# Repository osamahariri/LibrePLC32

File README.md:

# LibrePLC32

**LibrePLC32** is an open-source, KiCad-based Programmable Logic Controller (PLC) hardware project.

The goal of the project is to create a compact, hackable, and well-documented PLC platform for industrial automation experiments, prototyping, education, and open hardware development.

> ⚠️ **Work in progress:** LibrePLC32 is currently under development.

## Project goals

LibrePLC32 aims to provide:

- An open hardware PLC design
- KiCad source files for schematic and PCB development
- Field-oriented interfaces such as digital I/O, isolated CAN, isolated RS-485, and Ethernet
- A design that can be studied, modified, repaired, and improved by the community
- Documentation for design decisions and component calculations

## Repository structure

```text
.
├── img/              # Project logo and graphics
├── plc/
│   ├── docs/         # Design notes and calculations
│   └── kicad/        # KiCad project, schematics, PCB, and libraries
├── LICENSE
└── README.md
```

## Features

LibrePLC32 is designed to provide a practical set of PLC-oriented hardware features:

- **8–36 V DC input voltage range**
- **4 isolated digital inputs** for field signals
- **4 transistor digital outputs** for driving external loads
- **2 relay output terminals** for switching isolated loads
- **Isolated RS-485 interface** for industrial serial communication
- **Isolated CAN bus interface** for device-to-device communication
- **Ethernet interface** for network connectivity

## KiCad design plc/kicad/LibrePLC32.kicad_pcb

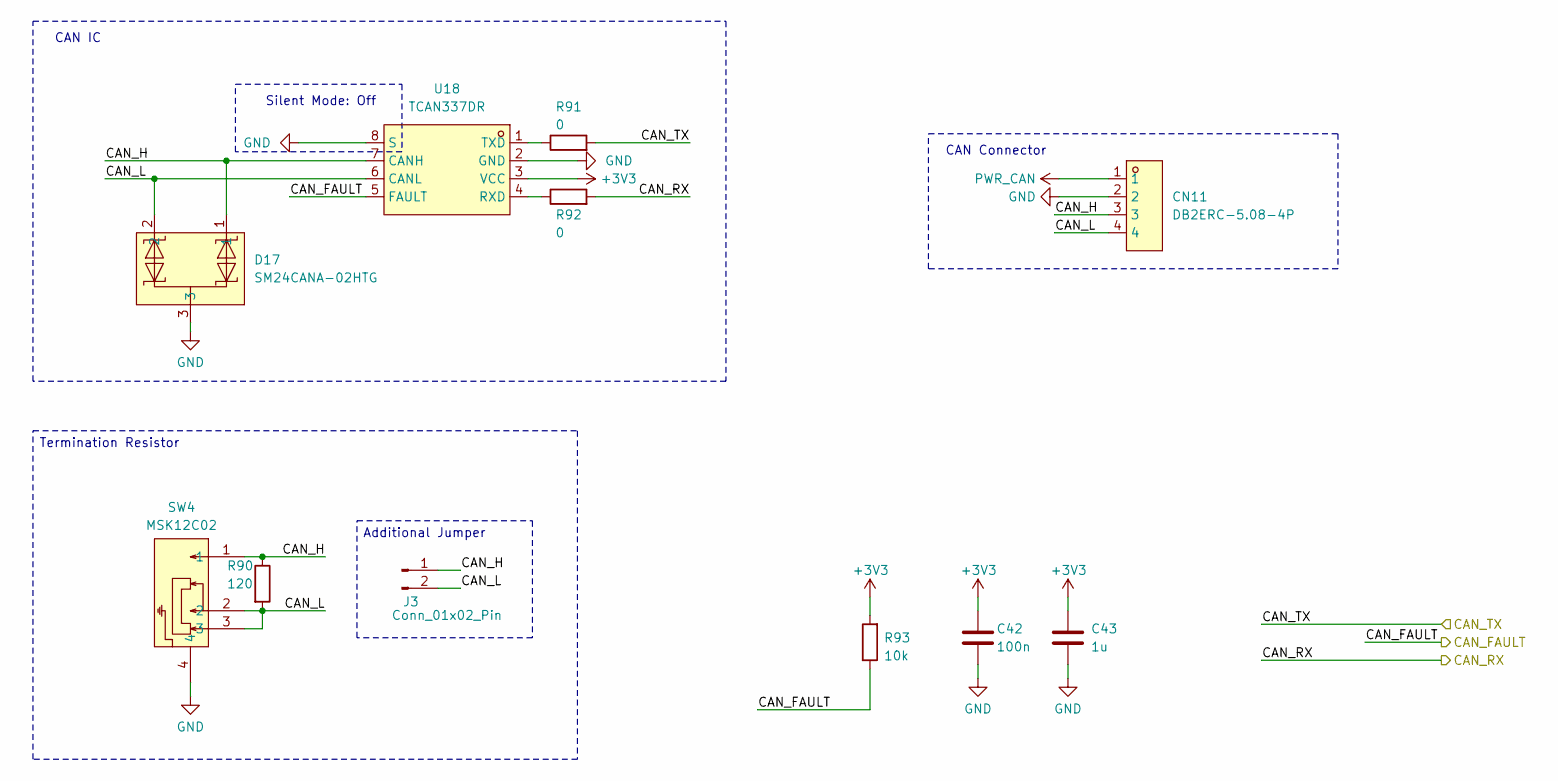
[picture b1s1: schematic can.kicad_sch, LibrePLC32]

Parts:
C42: 100n; C_0603_1608Metric
C43: 1u; C_0603_1608Metric
CN11: DB2ERC-5.08-4P; CONN-TH_4P-P5.08_DB2ERC-5.08-4P; MPN DB2ERC-5.08-4P-GN; LCSC Part C395753
D17: SM24CANA-02HTG; SOT-23_L2.9-W1.3-P1.90-LS2.4-BR; MPN SM24CANA-02HTG; LCSC Part C151236
J3: Conn_01x02_Pin; PinSocket_1x02_P2.54mm_Vertical
R90: 120; R_0603_1608Metric
R91, R92: 0; R_0603_1608Metric
R93: 10k; R_0603_1608Metric
SW4: MSK12C02; SW-TH_MSK12C02; MPN MSK12C02; LCSC Part C431540
U18: TCAN337DR; SOIC-8_L4.9-W3.9-P1.27-LS6.0-BL; MPN TCAN337DR; LCSC Part C2860648

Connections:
+3V3: C42.1, C43.1, R93.2, U18.3 (VCC); also elsewhere on the board
/CAN/CAN_FAULT: R93.1, U18.5 (FAULT); also elsewhere on the board
/CAN/CAN_H: CN11.3, D17.1, J3.1, R90.1, SW4.1, U18.7 (CANH)
/CAN/CAN_L: CN11.4, D17.2, J3.2, R90.2, SW4.2, SW4.3, U18.6 (CANL)
/CAN/CAN_RX: R92.2; also elsewhere on the board
/CAN/CAN_TX: R91.2; also elsewhere on the board
GND: C42.2, C43.2, CN11.2, D17.3, SW4.4, U18.2 (GND), U18.8 (S); also elsewhere on the board
unnamed: R92.1, U18.4 (RXD)
unnamed: R91.1, U18.1 (TXD)
PWR_CAN: CN11.1; also elsewhere on the board

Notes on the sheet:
CAN Connector
Additional Jumper
Termination Resistor
CAN IC
Silent Mode: Off

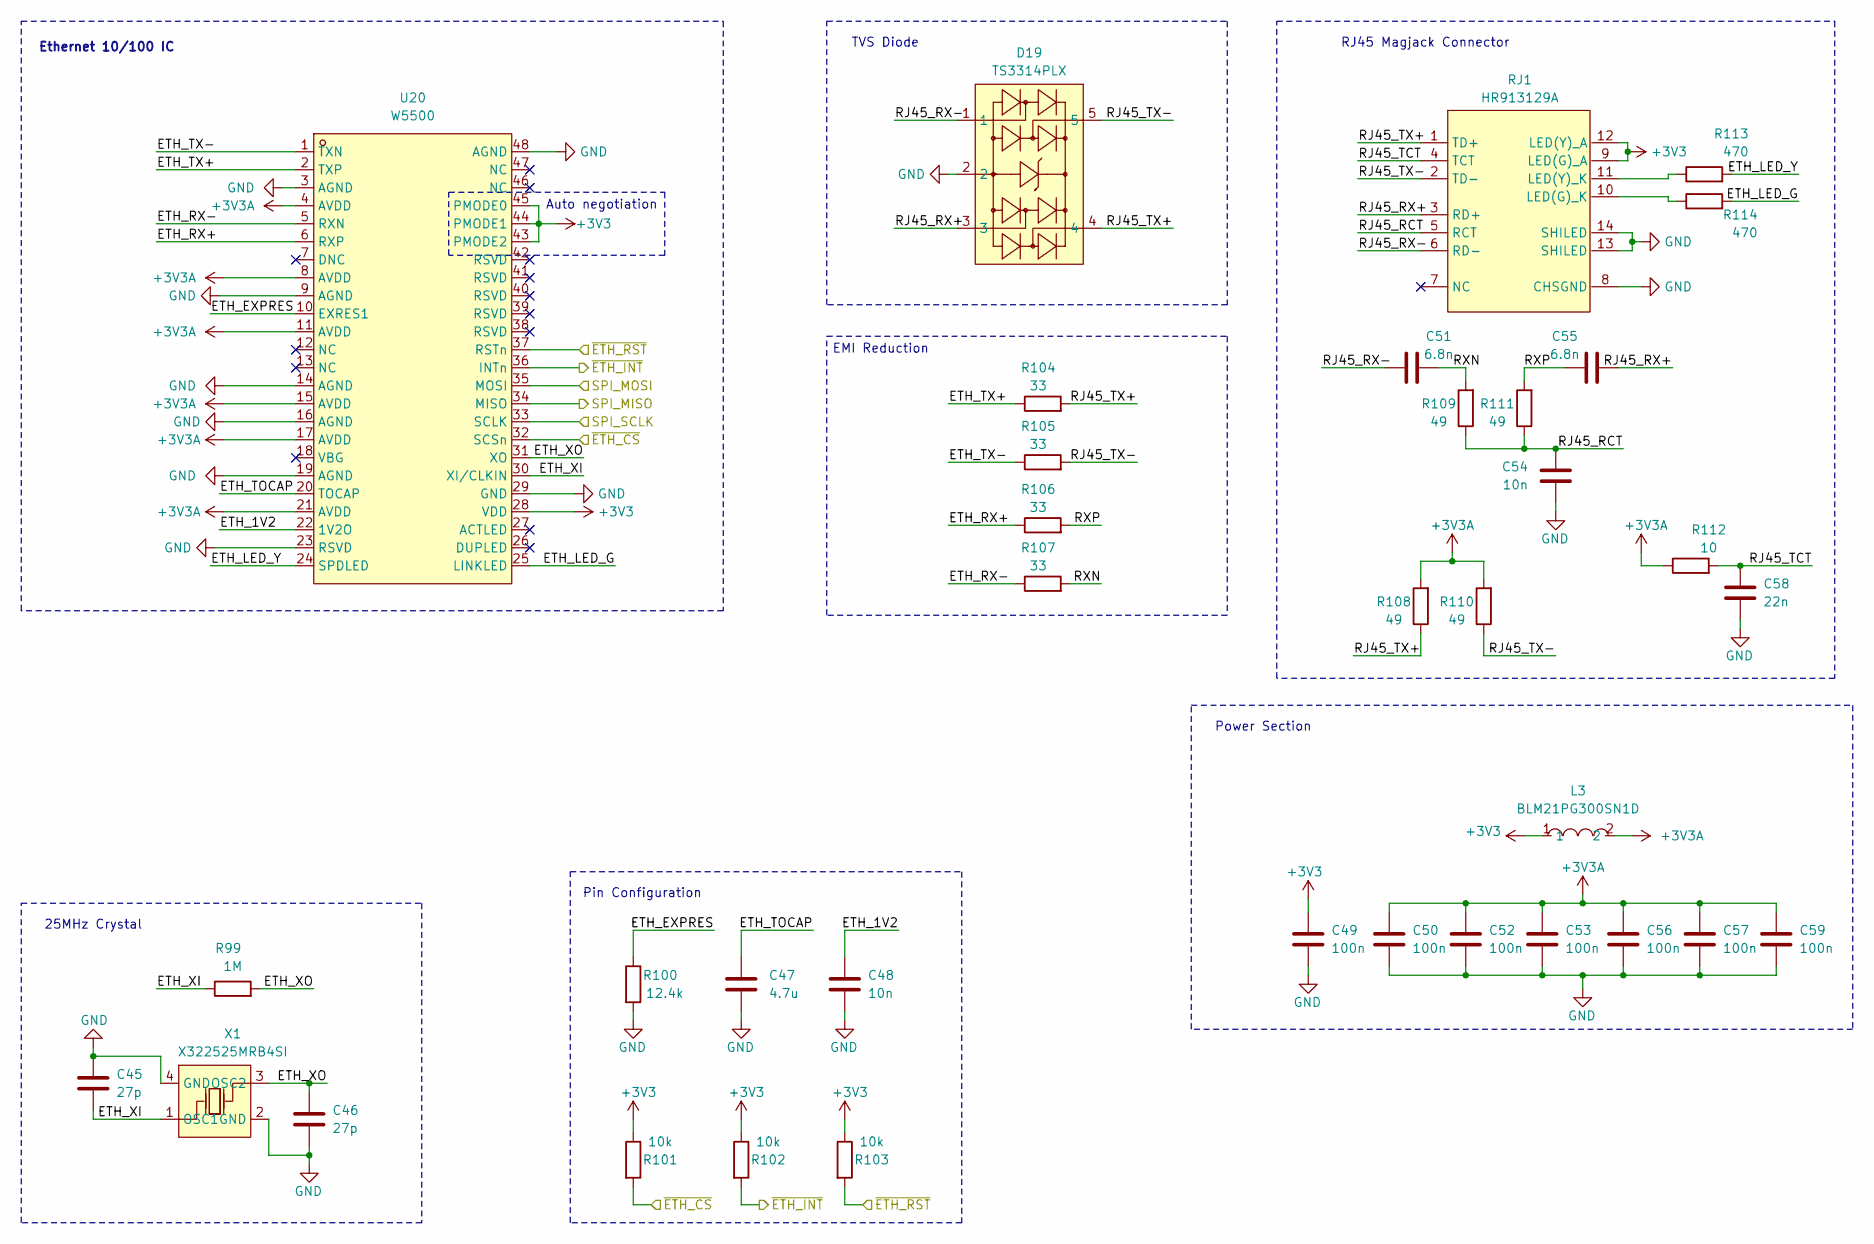
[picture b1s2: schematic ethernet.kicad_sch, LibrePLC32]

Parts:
C45, C46: 27p; C_0603_1608Metric
C47: 4.7u; C_0603_1608Metric
C48, C54: 10n; C_0603_1608Metric
C49, C50, C52, C53, C56, C57, C59: 100n; C_0603_1608Metric
C51, C55: 6.8n; C_0603_1608Metric
C58: 22n; C_0603_1608Metric
D19: TS3314PLX; SOT-23-5_L2.9-W1.6-P0.95-LS2.8-BR; MPN TS3314PLX; LCSC Part C5156700
L3: BLM21PG300SN1D; L0805; MPN BLM21PG300SN1D; LCSC Part C16903
R99: 1M; R_0603_1608Metric
R100: 12.4k; R_0603_1608Metric
R101, R102, R103: 10k; R_0603_1608Metric
R104, R105, R106, R107: 33; R_0603_1608Metric
R108, R109, R110, R111: 49; R_0603_1608Metric
R112: 10; R_0603_1608Metric
R113, R114: 470; R_0603_1608Metric
RJ1: HR913129A; RJ45-TH_HR913129A; MPN HR913129A; LCSC Part C70302
U20: W5500; LQFP-48_L7.0-W7.0-P0.50-LS9.0-BL; MPN W5500; LCSC Part C32843
X1: X322525MRB4SI; OSC-SMD_4P-L3.2-W2.5-BL_SIT8008BI; MPN X322525MRB4SI; LCSC Part C70593

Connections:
+3V3: C49.1, L3.1, R101.1, R102.1, R103.1, RJ1.9 (LED(G)_A), RJ1.12 (LED(Y)_A), U20.28 (VDD), U20.43 (PMODE2), U20.44 (PMODE1), U20.45 (PMODE0); also elsewhere on the board
+3V3A: C50.1, C52.1, C53.1, C56.1, C57.1, C59.1, L3.2, R108.2, R110.2, R112.1, U20.4 (AVDD), U20.8 (AVDD), U20.11 (AVDD), U20.15 (AVDD), U20.17 (AVDD), U20.21 (AVDD)
/Ethernet/ETH_1V2: C48.1, U20.22 (1V2O)
/Ethernet/ETH_EXPRES: R100.1, U20.10 (EXRES1)
/Ethernet/ETH_LED_G: R114.2, U20.25 (LINKLED)
/Ethernet/ETH_LED_Y: R113.2, U20.24 (SPDLED)
/Ethernet/ETH_RX+: R106.1, U20.6 (RXP)
/Ethernet/ETH_RX-: R107.1, U20.5 (RXN)
/Ethernet/ETH_TOCAP: C47.1, U20.20 (TOCAP)
/Ethernet/ETH_TX+: R104.1, U20.2 (TXP)
/Ethernet/ETH_TX-: R105.1, U20.1 (TXN)
/Ethernet/ETH_XI: C45.2, R99.1, U20.30 (XI/CLKIN), X1.1 (OSC1)
/Ethernet/ETH_XO: C46.1, R99.2, U20.31 (XO), X1.3 (OSC2)
/Ethernet/RJ45_RCT: C54.1, R109.1, R111.1, RJ1.5 (RCT)
/Ethernet/RJ45_RX+: C55.2, D19.3, RJ1.3 (RD+)
/Ethernet/RJ45_RX-: C51.2, D19.1, RJ1.6 (RD-)
/Ethernet/RJ45_TCT: C58.1, R112.2, RJ1.4 (TCT)
/Ethernet/RJ45_TX+: D19.4, R104.2, R108.1, RJ1.1 (TD+)
/Ethernet/RJ45_TX-: D19.5, R105.2, R110.1, RJ1.2 (TD-)
/Ethernet/RXN: C51.1, R107.2, R109.2
/Ethernet/RXP: C55.1, R106.2, R111.2
/Ethernet/SPI_MISO: U20.34 (MISO); also elsewhere on the board
/Ethernet/SPI_MOSI: U20.35 (MOSI); also elsewhere on the board
/Ethernet/SPI_SCLK: U20.33 (SCLK); also elsewhere on the board
/Ethernet/~ETH_CS: R101.2, U20.32 (SCSn); also elsewhere on the board
/Ethernet/~ETH_INT: R102.2, U20.36 (INTn); also elsewhere on the board
/Ethernet/~ETH_RST: R103.2, U20.37 (RSTn); also elsewhere on the board
GND: C45.1, C46.2, C47.2, C48.2, C49.2, C50.2, C52.2, C53.2, C54.2, C56.2, C57.2, C58.2, C59.2, D19.2, R100.2, RJ1.8 (CHSGND), RJ1.13 (SHILED), RJ1.14 (SHILED), U20.3 (AGND), U20.9 (AGND), U20.14 (AGND), U20.16 (AGND), U20.19 (AGND), U20.23 (RSVD), U20.29 (GND), U20.48 (AGND), X1.2 (GND), X1.4 (GND); also elsewhere on the board
unnamed: R114.1, RJ1.10 (LED(G)_K)
unnamed: R113.1, RJ1.11 (LED(Y)_K)

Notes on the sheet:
Auto negotiation
Ethernet 10/100 IC
EMI Reduction
TVS Diode
Power Section
Pin Configuration
25MHz Crystal
RJ45 Magjack Connector

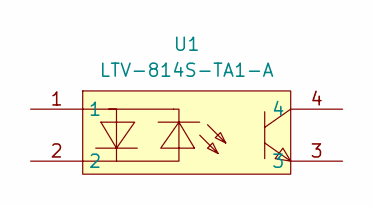
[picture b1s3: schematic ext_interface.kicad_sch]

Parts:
U1: LTV-814S-TA1-A; OPTO-SMD-4_L4.6-W6.5-P2.54-LS10.3-BL; MPN LTV-814S-TA1-A; LCSC Part C108051

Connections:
/Terminal Blocks Interface/T1_EN1: U1.4 (P00); also elsewhere on the board
/Terminal Blocks Interface/~GPIO_MUX_INT: U1.1 (~INT); also elsewhere on the board
GND: U1.2 (A1), U1.3 (A2); also elsewhere on the board

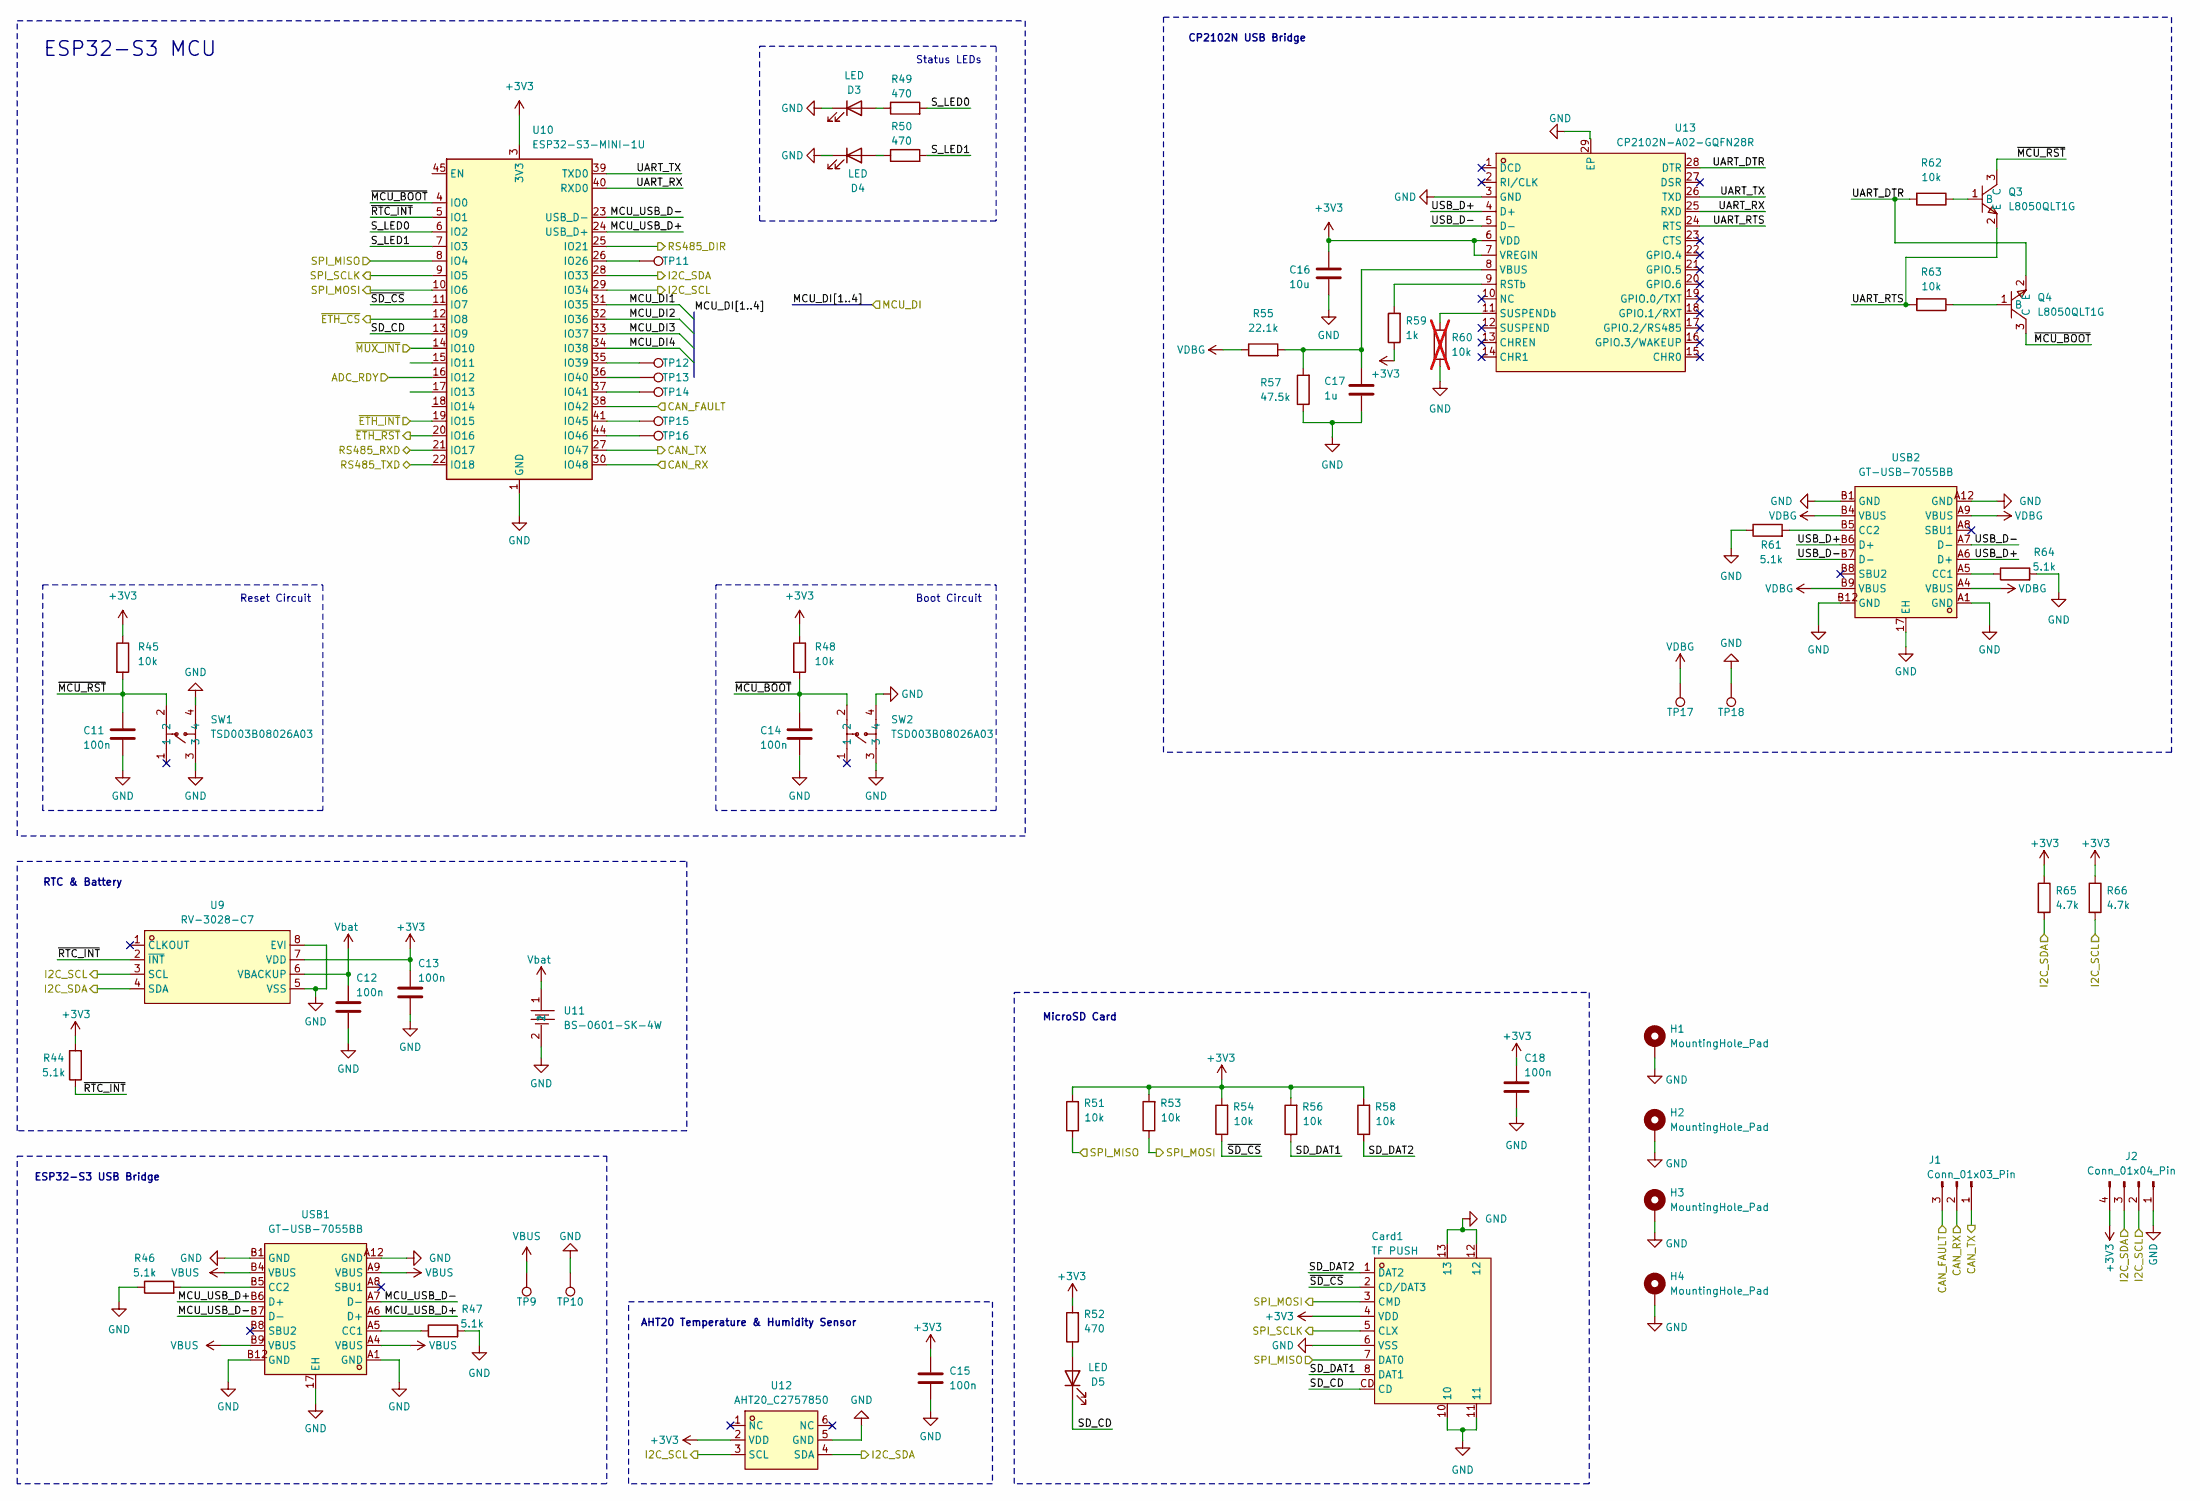
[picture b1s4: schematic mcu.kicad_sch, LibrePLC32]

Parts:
C11, C12, C13, C14, C15, C18: 100n; C_0603_1608Metric
C16: 10u; C_0603_1608Metric
C17: 1u; C_0603_1608Metric
Card1: TF PUSH; TF-SMD_TF-PUSH; MPN TF PUSH; LCSC Part C393941
D3, D4, D5: LED; LED_0805_2012Metric
H1, H2, H3, H4: MountingHole_Pad; MountingHole_4.3mm_M4_DIN965_Pad_TopBottom
J1: Conn_01x03_Pin
J2: Conn_01x04_Pin; PinSocket_1x04_P2.54mm_Vertical
Q3, Q4: L8050QLT1G; SOT-23-3_L2.9-W1.3-P1.90-LS2.4-BR; MPN L8050QLT1G; LCSC Part C49581
R44, R46, R47, R61, R64: 5.1k; R_0603_1608Metric
R45, R48, R51, R53, R54, R56, R58, R62, R63: 10k; R_0603_1608Metric
R49, R50, R52: 470; R_0603_1608Metric
R55: 22.1k; R_0603_1608Metric
R57: 47.5k; R_0603_1608Metric
R59: 1k; R_0603_1608Metric
R60: 10k; R_0603_1608Metric; not fitted
R65, R66: 4.7k; R_0603_1608Metric
SW1, SW2: TSD003B08026A03; SW-SMD_4P-L6.0-W6.0-P4.50-LS8.6; MPN TSD003B08026A03; LCSC Part C2888805
TP9, TP10, TP17, TP18: TestPoint; TestPoint_Pad_D3.0mm
TP11, TP12, TP13, TP14, TP15, TP16: TestPoint; TestPoint_Pad_D2.0mm
U9: RV-3028-C7; OSC-SMD_8P-L3.2-W1.5-P0.90-BL; MPN RV-3028-C7-32.768kHz-1ppm-TA-QC; LCSC Part C3019759
U10: ESP32-S3-MINI-1U; BULETM-SMD_ESPRESSIF_ESP32-S3-MINI-1U-N8
U11: BS-0601-SK-4W; BAT-SMD_BS-06-B4AA012; MPN BS-0601-SK-4W; LCSC Part C19089122
U12: AHT20_C2757850; SENSOR-SMD_L3.0-W3.0-P1.00-BR; MPN AHT20; LCSC Part C2757850
U13: CP2102N-A02-GQFN28R; QFN-28_L5.0-W5.0-P0.50-TL-EP3.3; MPN CP2102N-A02-GQFN28R; LCSC Part C964632
USB1, USB2: GT-USB-7055BB; USB-C-TH_GT-USB-7055BB; MPN GT-USB-7055BB; LCSC Part C7450621

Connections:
+3V3: C13.2, C15.1, C16.2, C18.2, Card1.4 (VDD), J2.4, R44.2, R45.1, R48.1, R51.2, R52.2, R53.2, R54.2, R56.2, R58.2, R59.1, R65.1, R66.1, U9.7 (VDD), U10.3 (3V3), U12.2 (VDD), U13.6 (VDD), U13.7 (VREGIN); also elsewhere on the board
/CAN/CAN_FAULT: J1.3, U10.38 (IO42); also elsewhere on the board
/CAN/CAN_RX: J1.2, U10.30 (IO48); also elsewhere on the board
/CAN/CAN_TX: J1.1, U10.27 (IO47); also elsewhere on the board
/Ethernet/SPI_MISO: Card1.7 (DAT0), R51.1, U10.8 (IO4); also elsewhere on the board
/Ethernet/SPI_MOSI: Card1.3 (CMD), R53.1, U10.10 (IO6); also elsewhere on the board
/Ethernet/SPI_SCLK: Card1.5 (CLX), U10.9 (IO5); also elsewhere on the board
/Ethernet/~ETH_CS: U10.12 (IO8); also elsewhere on the board
/Ethernet/~ETH_INT: U10.19 (IO15); also elsewhere on the board
/Ethernet/~ETH_RST: U10.20 (IO16); also elsewhere on the board
/MCU/ADC_RDY: U10.16 (IO12); also elsewhere on the board
/MCU/I2C_SCL: J2.2, R66.2, U9.3 (SCL), U10.29 (IO34), U12.3 (SCL); also elsewhere on the board
/MCU/I2C_SDA: J2.3, R65.2, U9.4 (SDA), U10.28 (IO33), U12.4 (SDA); also elsewhere on the board
/MCU/MCU_DI1: U10.31 (IO35); also elsewhere on the board
/MCU/MCU_DI2: U10.32 (IO36); also elsewhere on the board
/MCU/MCU_DI3: U10.33 (IO37); also elsewhere on the board
/MCU/MCU_DI4: U10.34 (IO38); also elsewhere on the board
/MCU/MCU_USB_D+: U10.24 (USB_D+), USB1.A6 (D+), USB1.B6 (D+)
/MCU/MCU_USB_D-: U10.23 (USB_D-), USB1.A7 (D-), USB1.B7 (D-)
/MCU/SD_CD: Card1.CD, D5.1 (K), U10.13 (IO9)
/MCU/SD_DAT1: Card1.8 (DAT1), R56.1
/MCU/SD_DAT2: Card1.1 (DAT2), R58.1
/MCU/S_LED0: R49.2, U10.6 (IO2)
/MCU/S_LED1: R50.2, U10.7 (IO3)
/MCU/UART_DTR: Q4.2 (E), R62.2, U13.28 (DTR)
/MCU/UART_RTS: Q3.2 (E), R63.2, U13.24 (RTS)
/MCU/UART_RX: U10.40 (RXD0), U13.25 (RXD)
/MCU/UART_TX: U10.39 (TXD0), U13.26 (TXD)
/MCU/USB_D+: U13.4 (D+), USB2.A6 (D+), USB2.B6 (D+)
/MCU/USB_D-: U13.5 (D-), USB2.A7 (D-), USB2.B7 (D-)
/MCU/~MCU_BOOT: C14.2, Q4.3 (C), R48.2, SW2.2, U10.4 (IO0)
/MCU/~MCU_RST: C11.2, Q3.3 (C), R45.2, SW1.2
/MCU/~RTC_INT: R44.1, U9.2 (~INT), U10.5 (IO1)
/MCU/~SD_CS: Card1.2 (CD/DAT3), R54.1, U10.11 (IO7)
/RS-485/RS485_DIR: U10.25 (IO21); also elsewhere on the board
/RS-485/RS485_RXD: U10.21 (IO17); also elsewhere on the board
/RS-485/RS485_TXD: U10.22 (IO18); also elsewhere on the board
/Terminal Blocks Interface/~GPIO_MUX_INT: U10.14 (IO10); also elsewhere on the board
GND: C11.1, C12.1, C13.1, C14.1, C15.2, C16.1, C17.2, C18.1, Card1.6 (VSS), Card1.10, Card1.11, Card1.12, Card1.13, D3.1 (K), D4.1 (K), H1.1 (1_1), H2.1 (1_1), H3.1 (1_1), H4.1 (1_1), J2.1, R46.1, R47.2, R57.1, R60.1, R61.1, R64.2, SW1.3, SW1.4, SW2.3, SW2.4, TP10.1 (1_1), TP18.1 (1_1), U9.5 (VSS), U9.8 (EVI), U10.1 (GND), U10.2 (GND), U10.42 (GND), U10.43 (GND), U10.46 (GND), U10.47 (GND), U10.48 (GND), U10.49 (GND), U10.50 (GND), U10.51 (GND), U10.52 (GND), U10.53 (GND), U10.54 (GND), U10.55 (GND), U10.56 (GND), U10.57 (GND), U10.58 (GND), U10.59 (GND), U10.60 (GND), U10.61 (GND), U10.62 (GND), U10.63 (GND), U10.64 (GND), U10.65 (GND), U11.2, U12.5 (GND), U13.3 (GND), U13.29 (EP), USB1.17 (EH), USB1.A1 (GND), USB1.A12 (GND), USB1.B1 (GND), USB1.B12 (GND), USB2.17 (EH), USB2.A1 (GND), USB2.A12 (GND), USB2.B1 (GND), USB2.B12 (GND); also elsewhere on the board
unnamed: D3.2 (A), R49.1
unnamed: D4.2 (A), R50.1
unnamed: D5.2 (A), R52.1
unnamed: Q3.1 (B), R62.1
unnamed: Q4.1 (B), R63.1
unnamed: TP11.1 (1_1), U10.26 (IO26)
unnamed: TP12.1 (1_1), U10.35 (IO39)
unnamed: TP13.1 (1_1), U10.36 (IO40)
unnamed: TP14.1 (1_1), U10.37 (IO41)
unnamed: TP15.1 (1_1), U10.41 (IO45)
unnamed: TP16.1 (1_1), U10.44 (IO46)
unnamed: R59.2, U13.9 (RSTb)
unnamed: R60.2, U13.11 (SUSPENDb)
unnamed: C17.1, R55.2, R57.2, U13.8 (VBUS)
unnamed: R47.1, USB1.A5 (CC1)
unnamed: R46.2, USB1.B5 (CC2)
unnamed: R64.1, USB2.A5 (CC1)
unnamed: R61.2, USB2.B5 (CC2)
VBUS: TP9.1 (1_1), USB1.A4 (VBUS), USB1.A9 (VBUS), USB1.B4 (VBUS), USB1.B9 (VBUS); also elsewhere on the board
VDBG: R55.1, TP17.1 (1_1), USB2.A4 (VBUS), USB2.A9 (VBUS), USB2.B4 (VBUS), USB2.B9 (VBUS); also elsewhere on the board
Vbat: C12.2, U9.6 (VBACKUP), U11.1

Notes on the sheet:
MicroSD Card
Status LEDs
AHT20 Temperature & Humidity Sensor
Reset Circuit
RTC & Battery
CP2102N USB Bridge
Boot Circuit
ESP32-S3 USB Bridge
ESP32-S3 MCU

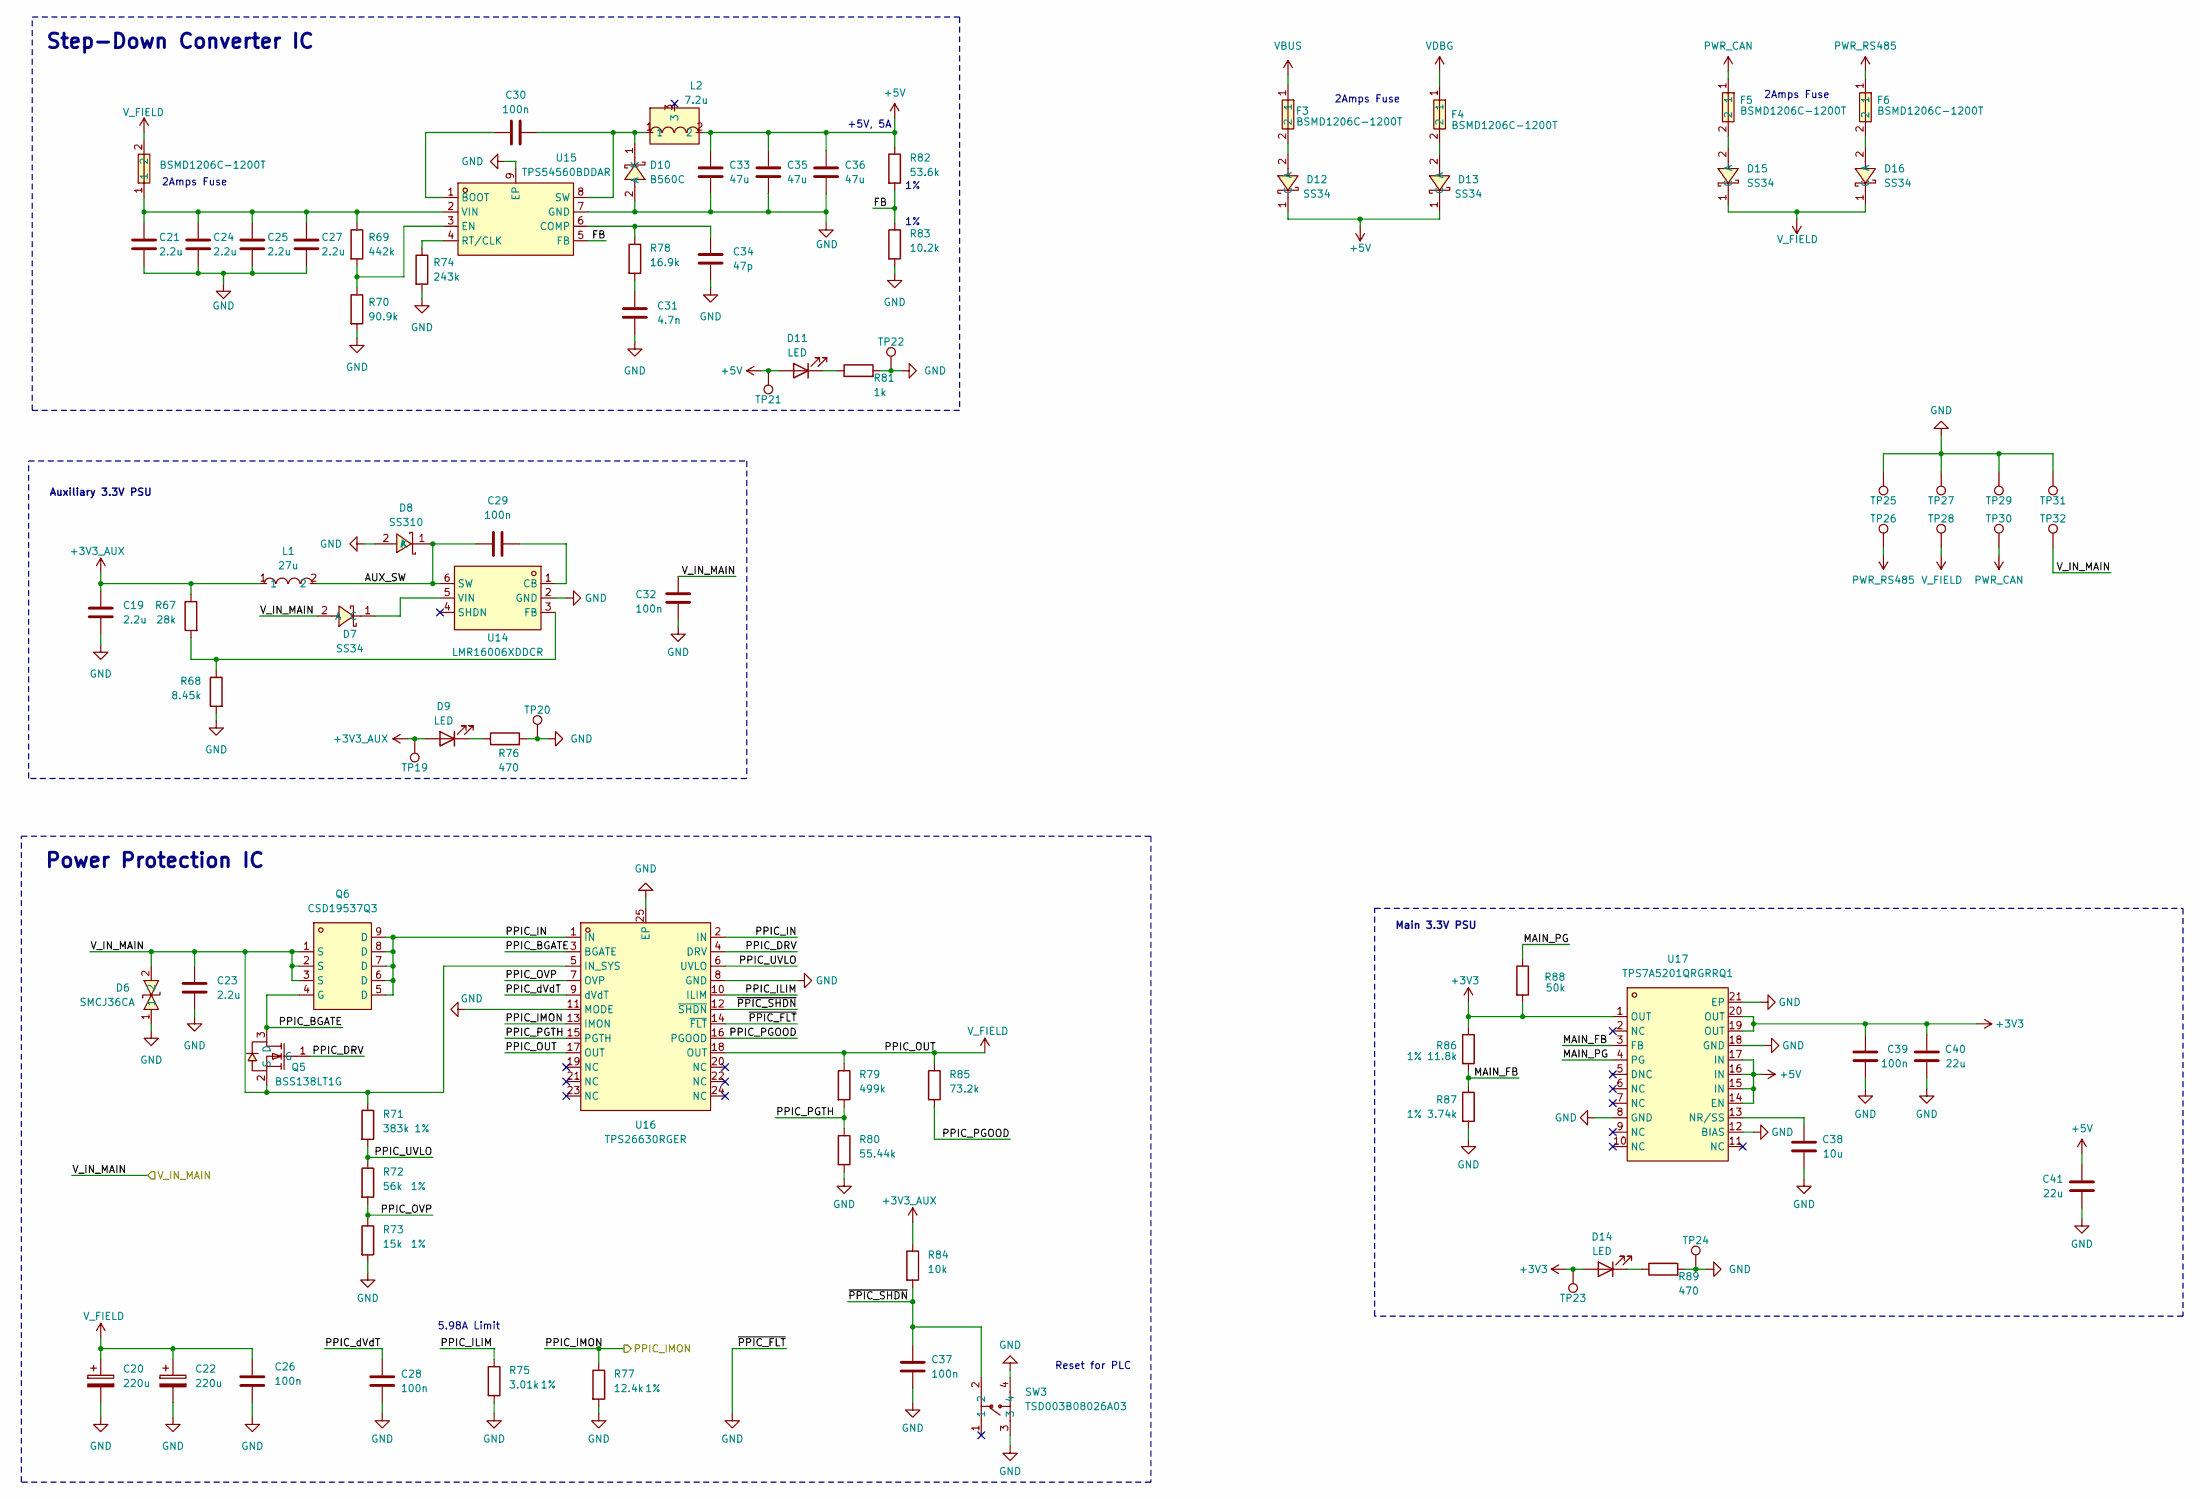
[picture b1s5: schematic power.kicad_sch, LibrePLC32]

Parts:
C19, C23: 2.2u; C_1206_3216Metric
C20, C22: 220u; C_Elec_10x10.2; LCSC Part C125977
C21, C24, C25, C27: 2.2u; C_0603_1608Metric
C26, C28, C29, C30, C32, C37, C39: 100n; C_0603_1608Metric
C31: 4.7n; C_0603_1608Metric
C33, C35, C36: 47u; C_0603_1608Metric
C34: 47p; C_0603_1608Metric
C38: 10u; C_0603_1608Metric
C40: 22u; C_0603_1608Metric; LCSC Part C86295
C41: 22u; C_0603_1608Metric
D6: SMCJ36CA; SMC_L6.9-W5.9-LS7.9-BI; MPN SMCJ36CA; LCSC Part C151283
D7, D12, D13, D15, D16: SS34; SMA_L4.3-W2.7-LS5.1-RD; MPN SS34; LCSC Part C908680
D8: SS310; SMB_L4.6-W3.6-LS5.3-RD; MPN SS310B; LCSC Part C14281
D9, D11, D14: LED; LED_0805_2012Metric
D10: B560C; SMC_L6.9-W5.9-LS7.9-RD; MPN B560C; LCSC Part C6807784
F2, F3, F4, F5, F6: BSMD1206C-1200T; F1206; MPN BSMD1206C-1200T; LCSC Part C41367223
L1: 27u; IND-SMD_L3.5-W3.0_SLF0302; MPN ASPI-0315S-270M-T; LCSC Part C187267
L2: 7.2u; IND-SMD_3P-L13.5-W13.0-P6.9; MPN XRCEP125-7R2M; LCSC Part C41368782
Q5: BSS138LT1G; SOT-23-3_L2.9-W1.6-P1.90-LS2.8-BR; MPN BSS138LT1G; LCSC Part C82045
Q6: CSD19537Q3; DFN-8_L3.3-W3.3-P0.65-BL-3; MPN CSD19537Q3; LCSC Part C478469
R67: 28k; R_0603_1608Metric
R68: 8.45k; R_0603_1608Metric
R69: 442k; R_0603_1608Metric
R70: 90.9k; R_0603_1608Metric
R71: 383k; R_0603_1608Metric; Tolerance 1%
R72: 56k; R_0603_1608Metric; Tolerance 1%
R73: 15k; R_0603_1608Metric; Tolerance 1%
R74: 243k; R_0603_1608Metric
R75: 3.01k; R_0603_1608Metric; Tolerance 1%
R76, R89: 470; R_0603_1608Metric
R77: 12.4k; R_0603_1608Metric; Tolerance 1%
R78: 16.9k; R_0603_1608Metric
R79: 499k; R_0603_1608Metric
R80: 55.44k; R_0603_1608Metric
R81: 1k; R_0603_1608Metric
R82: 53.6k; R_0603_1608Metric
R83: 10.2k; R_0603_1608Metric
R84: 10k; R_0603_1608Metric
R85: 73.2k; R_0603_1608Metric
R86: 11.8k; R_0603_1608Metric; Tolerance 1%
R87: 3.74k; R_0603_1608Metric; Tolerance 1%
R88: 50k; R_0603_1608Metric
SW3: TSD003B08026A03; SW-SMD_4P-L6.0-W6.0-P4.50-LS8.6; MPN TSD003B08026A03; LCSC Part C2888805
TP19, TP20, TP21, TP22, TP23, TP24: TestPoint; TestPoint_Pad_D3.0mm
TP25, TP26, TP27, TP28, TP29, TP30, TP31, TP32: TestPoint; TestPoint_Pad_D4.0mm
U14: LMR16006XDDCR; SOT-23-6_L2.9-W1.6-P0.95-LS2.8-BR; MPN LMR16006XDDCR; LCSC Part C87080
U15: TPS54560BDDAR; POWERPAD-SO-8_L4.9-W3.9-P1.27-LS6.0-BL-EP; MPN TPS54560BDDAR; LCSC Part C1850354
U16: TPS26630RGER; TQFN-24_L4.0-W4.0-P0.50-TL-EP; MPN TPS26630RGER(TOKMAS); LCSC Part C52940996
U17: TPS7A5201QRGRRQ1; VQFN-20_L3.5-W3.5-P0.50-TL-EP; MPN TPS7A5201QRGRRQ1; LCSC Part C523802

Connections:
+3V3: C39.2, C40.2, D14.2 (A), R86.1, R88.2, TP23.1 (1_1), U17.1 (OUT), U17.19 (OUT), U17.20 (OUT); also elsewhere on the board
+3V3_AUX: C19.1, D9.2 (A), L1.1, R67.1, R84.1, TP19.1 (1_1)
+5V: C33.2, C35.2, C36.2, C41.2, D11.2 (A), D12.1 (C), D13.1 (C), L2.2, R82.1, TP21.1 (1_1), U17.14 (EN), U17.15 (IN), U17.16 (IN), U17.17 (IN); also elsewhere on the board
/Power/AUX_SW: C29.2, D8.1 (K), L1.2, U14.6 (SW)
/Power/FB: R82.2, R83.1, U15.5 (FB)
/Power/MAIN_FB: R86.2, R87.1, U17.3 (FB)
/Power/MAIN_PG: R88.1, U17.4 (PG)
/Power/PPIC_BGATE: Q5.3 (D), Q6.4 (G), U16.3 (BGATE)
/Power/PPIC_DRV: Q5.1 (G), U16.4 (DRV)
/Power/PPIC_ILIM: R75.1, U16.10 (ILIM)
/Power/PPIC_IMON: R77.1, U16.13 (IMON); also elsewhere on the board
/Power/PPIC_IN: Q6.5 (D), Q6.6 (D), Q6.7 (D), Q6.8 (D), Q6.9 (D), U16.1 (IN), U16.2 (IN)
/Power/PPIC_OVP: R72.2, R73.1, U16.7 (OVP)
/Power/PPIC_PGOOD: R85.2, U16.16 (PGOOD)
/Power/PPIC_PGTH: R79.2, R80.1, U16.15 (PGTH)
/Power/PPIC_UVLO: R71.2, R72.1, U16.6 (UVLO)
/Power/PPIC_dVdT: C28.2, U16.9 (dVdT)
/Power/V_IN_MAIN: C23.2, C32.2, D6.2, D7.2 (A), Q5.2 (S), Q6.1 (S), Q6.2 (S), Q6.3 (S), R71.1, TP32.1 (1_1), U16.5 (IN_SYS); also elsewhere on the board
/Power/~PPIC_SHDN: C37.2, R84.2, SW3.2, U16.12 (~SHDN)
GND: C19.2, C20.2, C21.2, C22.2, C23.1, C24.2, C25.2, C26.1, C27.2, C28.1, C31.1, C32.1, C33.1, C34.1, C35.1, C36.1, C37.1, C38.1, C39.1, C40.1, C41.1, D6.1, D8.2 (A), D10.2 (A), R68.2, R70.2, R73.2, R74.2, R75.2, R76.2, R77.2, R80.2, R81.2, R83.2, R87.2, R89.2, SW3.3, SW3.4, TP20.1 (1_1), TP22.1 (1_1), TP24.1 (1_1), TP25.1 (1_1), TP27.1 (1_1), TP29.1 (1_1), TP31.1 (1_1), U14.2 (GND), U15.7 (GND), U15.9 (EP), U16.8 (GND), U16.11 (MODE), U16.14 (~FLT), U16.25 (EP), U17.8 (GND), U17.12 (BIAS), U17.18 (GND), U17.21 (EP); also elsewhere on the board
unnamed: C31.2, R78.2
unnamed: D7.1 (C), U14.5 (VIN)
unnamed: D9.1 (K), R76.1
unnamed: C30.2, D10.1 (K), L2.1, U15.8 (SW)
unnamed: D11.1 (K), R81.1
unnamed: D12.2 (A), F3.2
unnamed: D13.2 (A), F4.2
unnamed: D14.1 (K), R89.1
unnamed: D15.2 (A), F5.2
unnamed: D16.2 (A), F6.2
unnamed: C29.1, U14.1 (CB)
unnamed: R67.2, R68.1, U14.3 (FB)
unnamed: C30.1, U15.1 (BOOT)
unnamed: C34.2, R78.1, U15.6 (COMP)
unnamed: R69.2, R70.1, U15.3 (EN)
unnamed: R74.1, U15.4 (RT/CLK)
unnamed: C21.1, C24.1, C25.1, C27.1, F2.1, R69.1, U15.2 (VIN)
unnamed: C38.2, U17.13 (NR/SS)
PWR_CAN: F5.1, TP30.1 (1_1); also elsewhere on the board
PWR_RS485: F6.1, TP26.1 (1_1); also elsewhere on the board
VBUS: F3.1; also elsewhere on the board
VDBG: F4.1; also elsewhere on the board
V_FIELD: C20.1, C22.1, C26.2, D15.1 (C), D16.1 (C), F2.2, R79.1, R85.1, TP28.1 (1_1), U16.17 (OUT), U16.18 (OUT); also elsewhere on the board

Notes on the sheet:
Step-Down Converter IC
2Amps Fuse
Main 3.3V PSU
Reset for PLC
+5V, 5A
Power Protection IC
5.98A Limit
Auxiliary 3.3V PSU

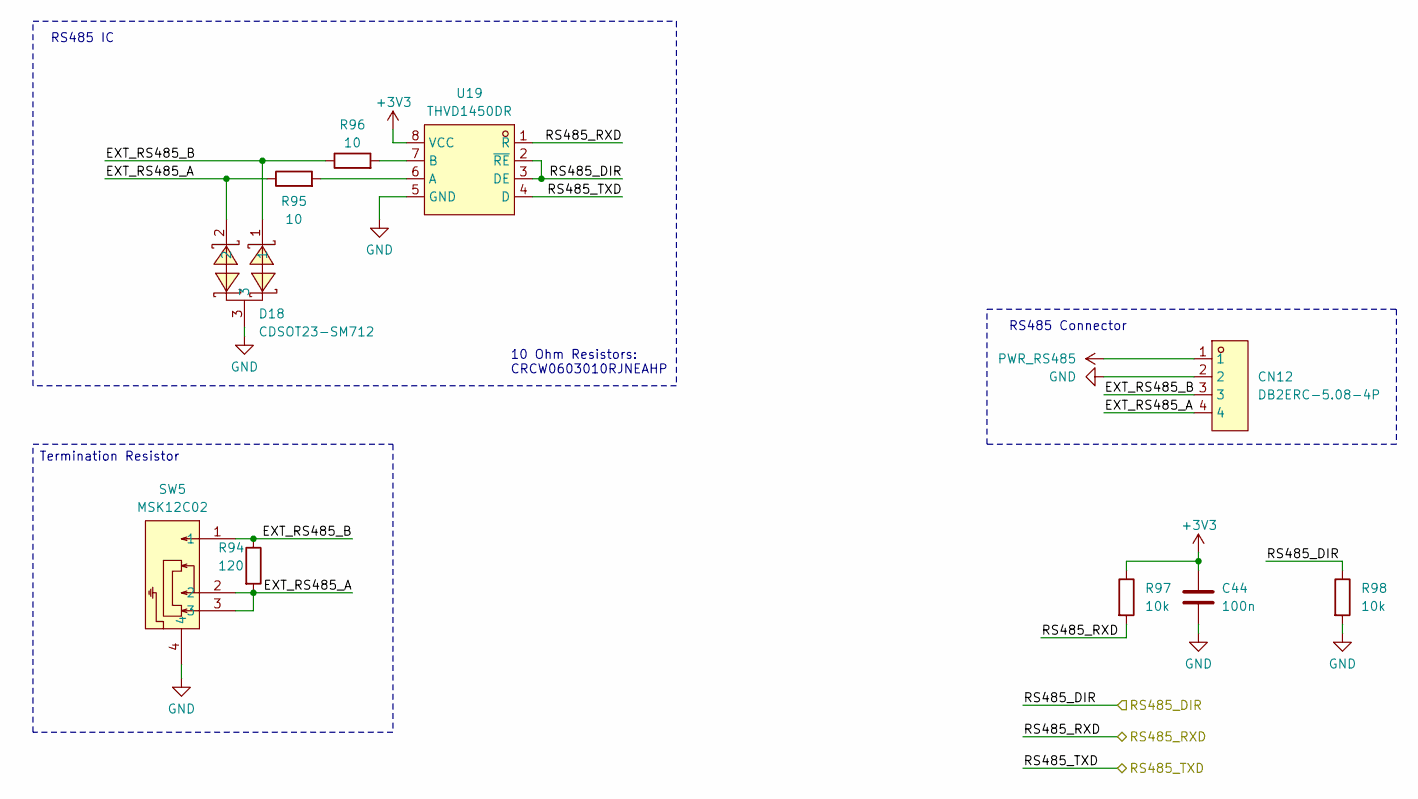
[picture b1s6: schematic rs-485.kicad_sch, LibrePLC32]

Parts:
C44: 100n; C_0603_1608Metric
CN12: DB2ERC-5.08-4P; CONN-TH_4P-P5.08_DB2ERC-5.08-4P; MPN DB2ERC-5.08-4P-GN; LCSC Part C395753
D18: CDSOT23-SM712; SOT-23_L2.9-W1.3-P1.90-LS2.4-BR; MPN CDSOT23-SM712; LCSC Part C404012
R94: 120; R_0603_1608Metric
R95, R96: 10; R_0603_1608Metric
R97, R98: 10k; R_0603_1608Metric
SW5: MSK12C02; SW-TH_MSK12C02; MPN MSK12C02; LCSC Part C431540
U19: THVD1450DR; SOIC-8_L4.9-W3.9-P1.27-LS6.0-BL; MPN THVD1450DR; LCSC Part C2671361

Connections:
+3V3: C44.1, R97.1, U19.8 (VCC); also elsewhere on the board
/RS-485/EXT_RS485_A: CN12.4, D18.2, R94.2, R95.1, SW5.2, SW5.3
/RS-485/EXT_RS485_B: CN12.3, D18.1, R94.1, R96.1, SW5.1
/RS-485/RS485_DIR: R98.1, U19.2 (~RE), U19.3 (DE); also elsewhere on the board
/RS-485/RS485_RXD: R97.2, U19.1 (R); also elsewhere on the board
/RS-485/RS485_TXD: U19.4 (D); also elsewhere on the board
GND: C44.2, CN12.2, D18.3, R98.2, SW5.4, U19.5 (GND); also elsewhere on the board
unnamed: R95.2, U19.6 (A)
unnamed: R96.2, U19.7 (B)
PWR_RS485: CN12.1; also elsewhere on the board

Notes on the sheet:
RS485 IC
Termination Resistor
10 Ohm Resistors: CRCW0603010RJNEAHP
RS485 Connector
